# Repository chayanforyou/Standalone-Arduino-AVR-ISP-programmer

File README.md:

# Standalone AVR programmer (GimmeSoul)

GimmeSoul is a standalone (no computer needed) bootloader programmer for ATmega328P. It can be used to facilitate programming of chips used by [Arduino UNO](https://store.arduino.cc/usa/arduino-uno-rev3) and [Senaino](https://github.com/import-tiago/Senaino), for example. 

This makes the process of flash the ICs so much faster than conventional way and eliminates the need for a computer.

## Mounted PCB

## PCB Gerber Preview

## Schematic

## Bill of Materials
To mount the components on the board, follow the instructions: [Designator References](https://github.com/import-tiago/GimmeSoul/blob/master/Hardware/1.%20Mounting/Silk%20Screen.png)

| Qty | Parts | Description | Value | Package |
|--|--|--|--|--|
2|R2/R3|SMD Resistor|100R ±5%|R0805
1|R1|SMD Resistor|10k ±5%|R0805
4|C1/C2/C4/C6|SMD Capacitor|100 nF / 50V|C0805
2|C3/C5|SMD Capacitor|1 uF / 50V|C0805
2|C7/C8|SMD Capacitor|22 pF / 50V|C0805
1|D2|SMD Diode|1N4007|SOD123
1|U1|SMD Microcontroller|ATmega328P|TQFP-32
1|U2|SMD Voltage Regulator|LM1117MP-5.0|SOT223
2|S1/S2|PTH Tact Switch|DPST|6 x 6 mm
1|Q1|PTH Crystal|16 MHz|HC49/S
1|SG5|PTH Buzzer|5V Passive|F/QMBIII
1|LED1|PTH LED|Green|5 mm
1|LED2|PTH LED|Red|5 mm
2|JP1/JP4|PTH Pin Header|Male 180°|1X08
1|JP2|PTH Pin Header|Male 180°|1X10
1|JP3|PTH Pin Header|Male 180°|1X06
1|ZX1|PTH ZIF socket|28-pin|Slim Width

## How To
[SETUP Tutorial](https://github.com/import-tiago/GimmeSoul/wiki/SETUP)

## Video
[# GimmeSoul - Demo](https://vimeo.com/363052289?activityReferer=1)

### Contributing
0. Give this project a :star:
1. Create an issue and describe your idea.
2. [Fork it](https://github.com/import-tiago/GimmeSoul/fork).
3. Create your feature branch (`git checkout -b my-new-feature`).
4. Commit your changes (`git commit -a -m "Added feature title"`).
5. Publish the branch (`git push origin my-new-feature`).
6. Create a new pull request.
7. Done! :heavy_check_mark:

### License Information
<br /><span xmlns:dct="http://purl.org/dc/terms/" property="dct:title">GimmeSoul</span> by <a xmlns:cc="http://creativecommons.org/ns#" href="https://github.com/import-tiago" property="cc:attributionName" rel="cc:attributionURL">Tiago Silva</a> is licensed under a <a rel="license" href="http://creativecommons.org/licenses/by-sa/4.0/">Creative Commons Attribution-ShareAlike 4.0 International License</a>.<br />Based on a work at <a xmlns:dct="http://purl.org/dc/terms/" href="[Standalone AVR Chip Programmer](https://learn.adafruit.com/standalone-avr-chip-programmer/)" rel="dct:source">[Standalone AVR Chip Programmer](https://learn.adafruit.com/standalone-avr-chip-programmer/)</a>.<br />Permissions beyond the scope of this license may be available at <a xmlns:cc="http://creativecommons.org/ns#" href="https://twitter.com/import_tiago" rel="cc:morePermissions">tiagodepaulasilva@gmail.com</a>.

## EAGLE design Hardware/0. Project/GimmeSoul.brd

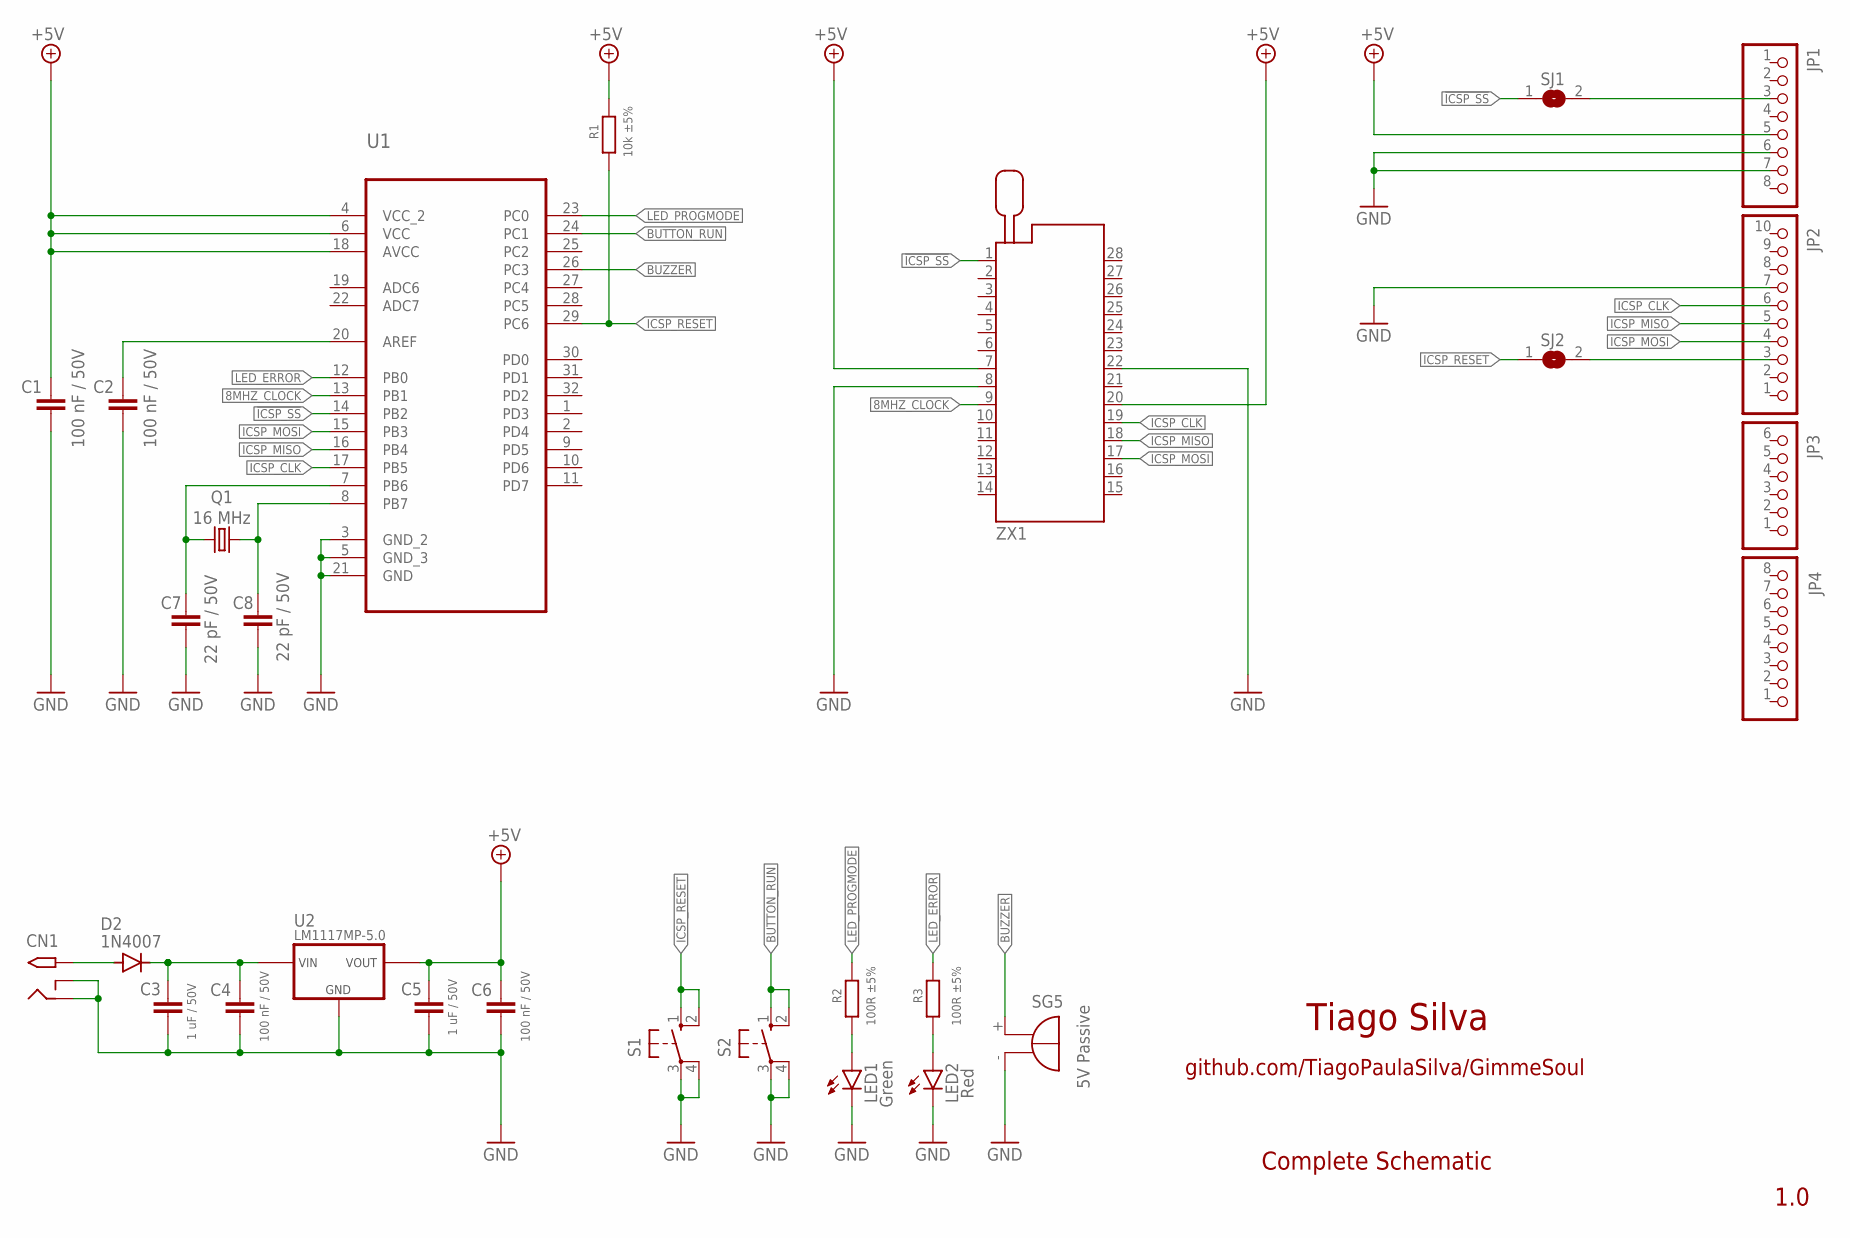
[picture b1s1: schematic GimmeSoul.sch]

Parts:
C1, C2, C4, C6: 100 nF / 50V; C0805
C3, C5: 1 uF / 50V; C0805
C7, C8: 22 pF / 50V; C0805
CN1: 2.1MMJACKTHM; PJ-102A
D2: 1N4007; SOD123
JP1, JP4: PINHD-1X8; 1X08
JP2: PINHD-1X10_ARD; 1X10
JP3: PINHD-1X6; 1X06
LED1: Green; LED5MM
LED2: Red; LED5MM
Q1: 16 MHz; HC49/S
R1: 10k ±5%; R0805
R2, R3: 100R ±5%; R0805
S1, S2: 10-XX; B3F-10XX
SG5: 5V Passive; F/QMBIII
SJ1, SJ2: SJ
U1: ATMEGA328P-AU; QFP80P900X900X120-32N
U2: LM1117MP-5.0; SOT223
ZX1: 228-4817-00-0602J

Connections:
8MHZ_CLOCK: U1.13 (PB1), ZX1.9
!ICSP_SS: SJ1.1, U1.14 (PB2), ZX1.1
+5V: C1.2, C5.1, C6.1, JP1.5, R1.1, U1.4 (VCC_2), U1.6 (VCC), U1.18 (AVCC), U2.2 (VOUT), U2.4 (VOUT), ZX1.7, ZX1.20
BUTTON_RUN: S2.1 (S), S2.2 (S1), U1.24 (PC1)
BUZZER: SG5.+ (-), U1.26 (PC3)
GND: C1.1, C2.1, C3.2, C4.2, C5.2, C6.2, C7.1, C8.1, CN1.RING, CN1.RING_SW, JP1.6, JP1.7, JP2.7, LED1.K (C), LED2.K (C), S1.3, S1.4 (P1), S2.3, S2.4 (P1), SG5.- (+), U1.3 (GND_2), U1.5 (GND_3), U1.21 (GND), U2.1 (GND), ZX1.8, ZX1.22
ICSP_CLK: JP2.6, U1.17 (PB5), ZX1.19
ICSP_MISO: JP2.5, U1.16 (PB4), ZX1.18
ICSP_MOSI: JP2.4, U1.15 (PB3), ZX1.17
ICSP_RESET: R1.2, S1.1 (S), S1.2 (S1), SJ2.1, U1.29 (PC6)
LED_ERROR: R3.1, U1.12 (PB0)
LED_PROGMODE: R2.1, U1.23 (PC0)
unnamed: LED1.A, R2.2
unnamed: CN1.TIP, D2.A
unnamed: LED2.A, R3.2
unnamed: C3.1, C4.1, D2.C, U2.3 (VIN)
unnamed: JP2.3, SJ2.2
unnamed: JP1.3, SJ1.2
unnamed: C7.2, Q1.1, U1.7 (PB6)
unnamed: C8.2, Q1.2, U1.8 (PB7)
unnamed: C2.2, U1.20 (AREF)

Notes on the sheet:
Tiago Silva
github.com/TiagoPaulaSilva/GimmeSoul
1.0
Complete Schematic

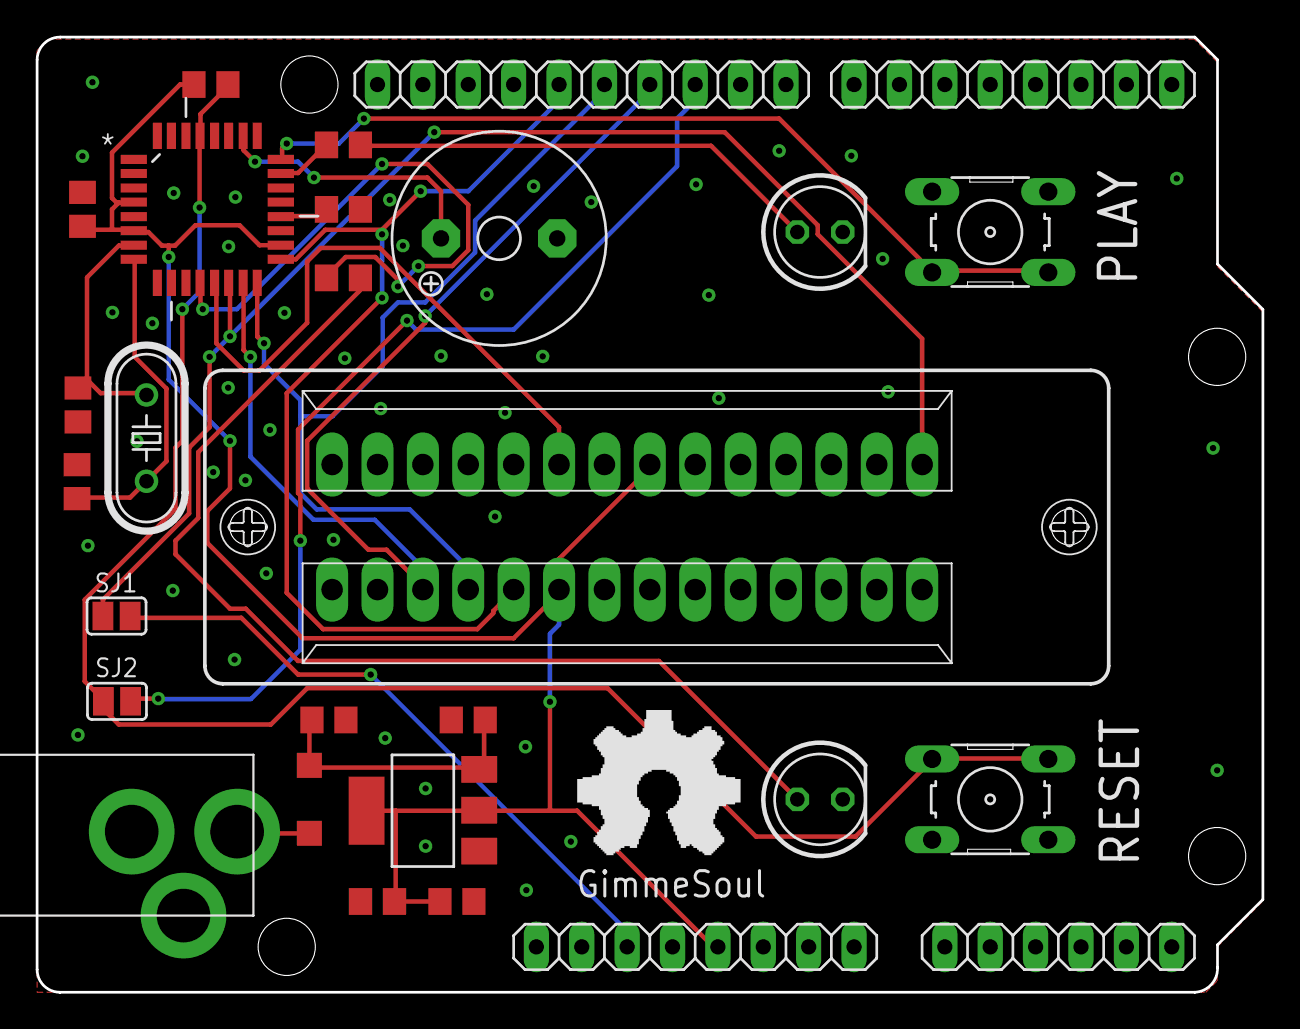
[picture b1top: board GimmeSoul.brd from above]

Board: 2 copper layers, 68.6 x 53.5 mm, 28 parts (0 on the bottom side), 21 nets.

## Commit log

2019-08-27 Directory restructuring
2019-08-27 Schematic designed
2019-08-27 Addes .gitattributes
2019-08-27 Schematic minor improvements
2019-08-27 Programing Status Effects Updated
2019-08-27 Jumper SJ1 and Button Reset S1 added
2019-08-28 .gitattributes updated
2019-08-28 .gitattributes removed
2019-08-28 External power supply support added
2019-08-28 PCB design done
2019-08-28 PCB layout minor improvements
2019-08-28 Schamatic image exported
2019-08-28 Jumpers on PCB layout bug fix
2019-08-28 Arduino pinouts diagram pdf added
2019-08-28 16MHz crystal added to MCU
2019-09-29 Silk Screen ref generated
2019-09-29 Set theme jekyll-theme-leap-day
2019-11-16 New images added
2020-07-17 .gitattributes added
2023-07-21 usernames in URLs updated
2023-09-16 Fix bug for no 128 byte page size
